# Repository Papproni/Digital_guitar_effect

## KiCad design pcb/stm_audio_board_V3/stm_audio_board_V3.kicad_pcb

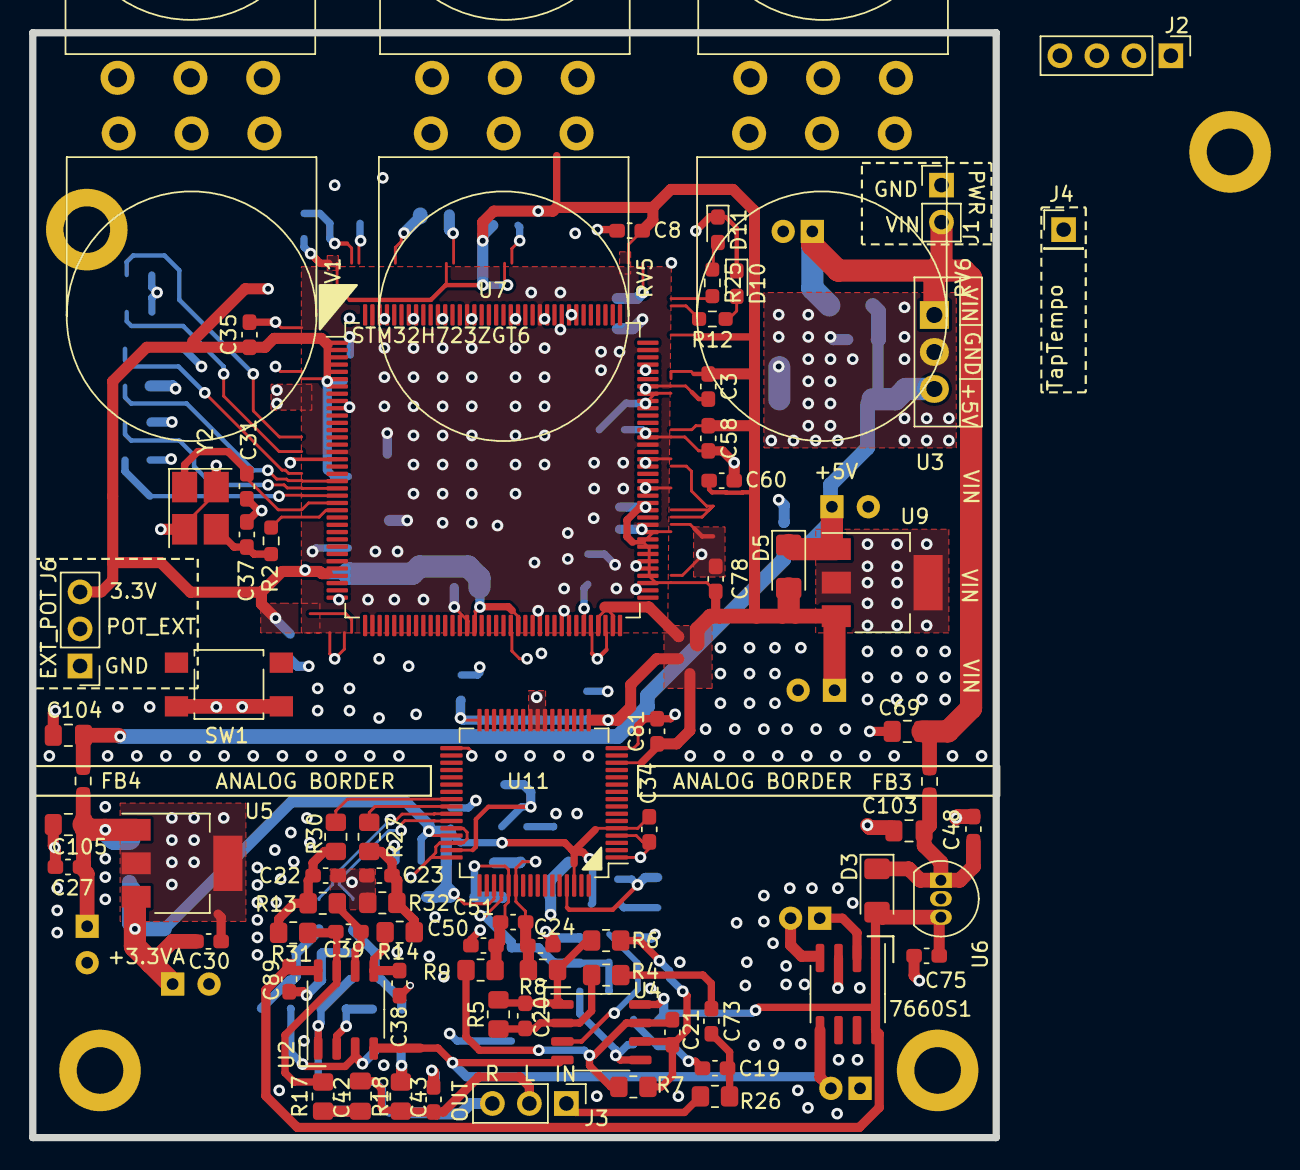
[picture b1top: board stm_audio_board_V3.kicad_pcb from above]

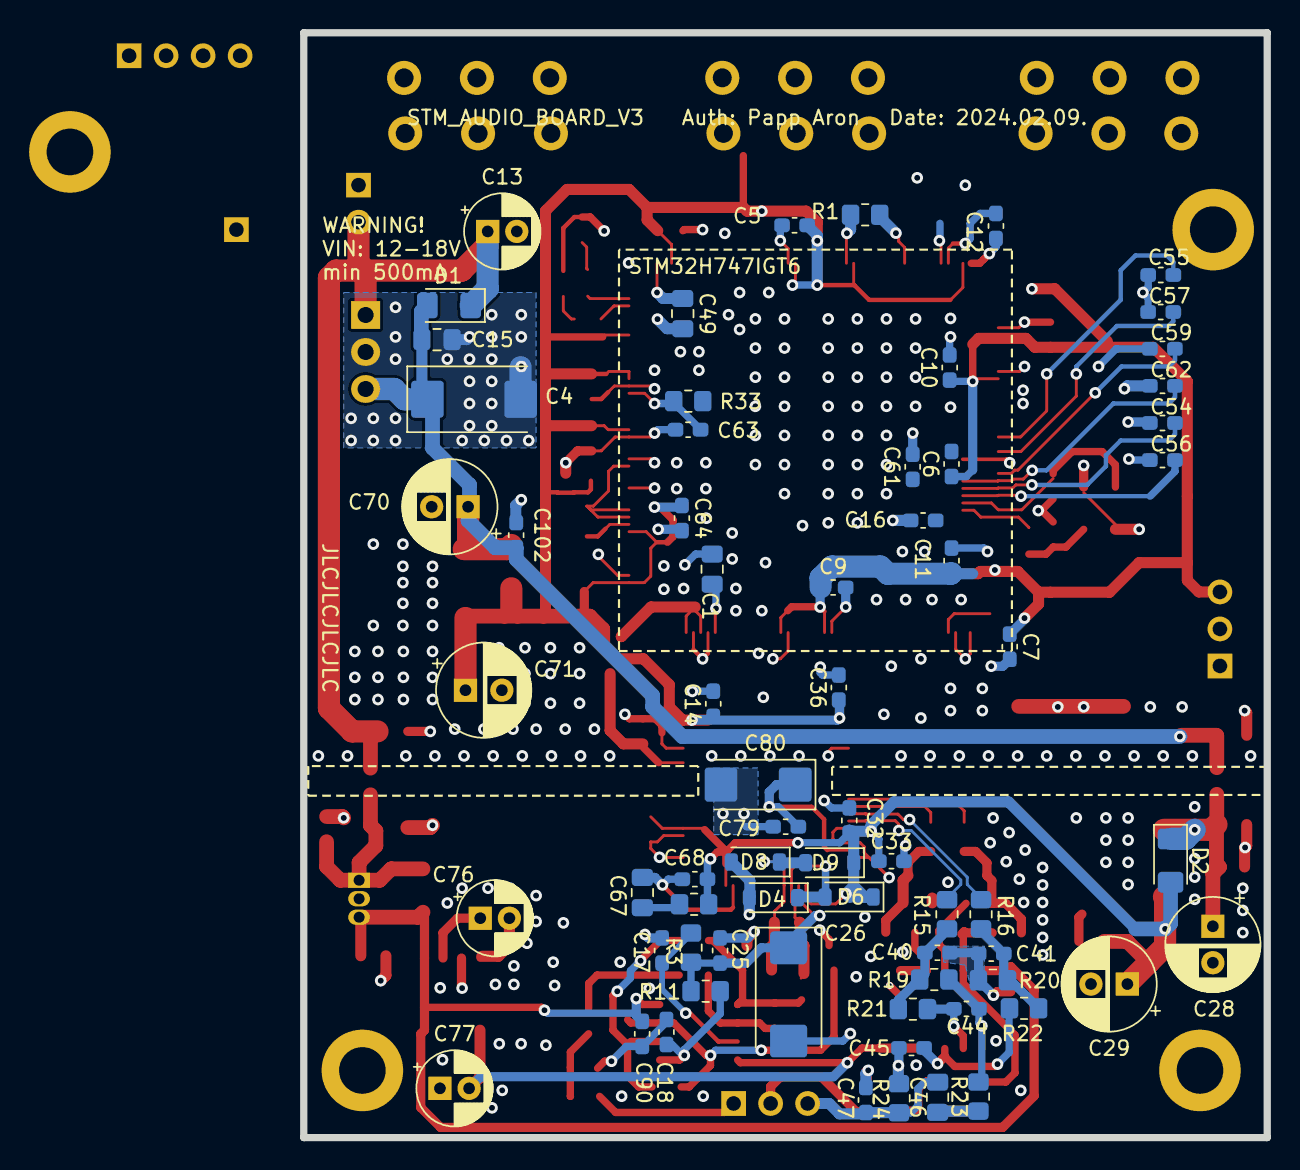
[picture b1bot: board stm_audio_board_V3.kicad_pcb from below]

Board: 4 copper layers, 66.1 x 75.8 mm, 149 parts (67 on the bottom side), 71 nets.

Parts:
7660S1: SOIC-8_3.9x4.9mm_P1.27mm
C1, C49: 2.2uF; C_0805_2012Metric_Pad1.18x1.45mm_HandSolder
C3, C5, C6, C7, C8, C9, C10, C11, C12, C14, C16, C25, C27, C30, C32, C33, C34, C35, C36, C48, C54, C55, C56, C57, C58, C59, C60, C61, C62, C63, C64, C75, C78, C79, C81, C89, C90, C102: 100nF; C_0603_1608Metric_Pad1.08x0.95mm_HandSolder
C4: 22uF tantal; CP_EIA-7343-31_Kemet-D_Pad2.25x2.55mm_HandSolder
C13: 22uF 50V poly; CP_Radial_D5.0mm_P2.00mm
C15, C69, C103, C104, C105: 2u2F; C_0805_2012Metric_Pad1.18x1.45mm_HandSolder
C17, C18, C73: 68n; C_0603_1608Metric_Pad1.08x0.95mm_HandSolder
C19, C20: 10p; C_0603_1608Metric_Pad1.08x0.95mm_HandSolder
C21: 120p; C_0603_1608Metric_Pad1.08x0.95mm_HandSolder
C22, C40: 270p; C_0603_1608Metric_Pad1.08x0.95mm_HandSolder
C23, C41: 560p; C_0603_1608Metric_Pad1.08x0.95mm_HandSolder
C24, C50: 1nF; C_0603_1608Metric_Pad1.08x0.95mm_HandSolder
C26: 47uF tantal; CP_EIA-7343-31_Kemet-D_Pad2.25x2.55mm_HandSolder
C28, C70: 100uF; CP_Radial_D6.3mm_P2.50mm
C29: 47uF; CP_Radial_D6.3mm_P2.50mm
C31, C37: 9pF; C_0603_1608Metric_Pad1.08x0.95mm_HandSolder
C38, C39, C44, C45: 68p; C_0603_1608Metric_Pad1.08x0.95mm_HandSolder
C42, C46: 2u2; C_0805_2012Metric_Pad1.18x1.45mm_HandSolder
C43, C47, C68: 2.2nF; C_0603_1608Metric_Pad1.08x0.95mm_HandSolder
C51: 100pF; C_0603_1608Metric_Pad1.08x0.95mm_HandSolder
C67: 39nF; C_0805_2012Metric_Pad1.18x1.45mm_HandSolder
C71: 47uf; CP_Radial_D6.3mm_P2.50mm
C76, C77: 10uF; CP_Radial_D5.0mm_P2.00mm
C80: 10uF tantal; CP_EIA-6032-28_Kemet-C_Pad2.25x2.35mm_HandSolder
D1, D2, D3, D5: 1N4148; D_1206_3216Metric_Pad1.42x1.75mm_HandSolder
D4, D6, D8, D9: BAT42W-V; D_SOD-123
D10, D11: LED; LED_0603_1608Metric_Pad1.05x0.95mm_HandSolder
FB3, FB4: TDK MMZ1608R601ATD25 DB; R_0603_1608Metric_Pad0.98x0.95mm_HandSolder
H1, H2, H3, H4: MountingHole_Pad; MountingHole_3.2mm_M3_DIN965_Pad
J1: Power conn; PinHeader_1x02_P2.54mm_Vertical
J2: STlink; PinHeader_1x04_P2.54mm_Vertical
J3: Audio_sig; PinHeader_1x03_P2.54mm_Vertical
J4: Conn_01x01_taptempo; PinHeader_1x01_P2.54mm_Vertical
J6: Conn_01x03_pot_ext; PinHeader_1x03_P2.54mm_Vertical
R1, R18, R24: 10k; R_0805_2012Metric_Pad1.20x1.40mm_HandSolder
R2: 100R NC; R_0603_1608Metric_Pad0.98x0.95mm_HandSolder
R3, R11: 100R; R_0805_2012Metric_Pad1.20x1.40mm_HandSolder
R4, R33: 500k; R_0805_2012Metric_Pad1.20x1.40mm_HandSolder
R5: 1M; R_0805_2012Metric_Pad1.20x1.40mm_HandSolder
R6, R7: 5.76k; R_0805_2012Metric_Pad1.20x1.40mm_HandSolder
R8, R9: 240R; R_0805_2012Metric_Pad1.20x1.40mm_HandSolder
R10: 3.32k; R_0805_2012Metric_Pad1.20x1.40mm_HandSolder
R12: 1k NC; R_0603_1608Metric_Pad0.98x0.95mm_HandSolder
R13, R21: 3k; R_0805_2012Metric_Pad1.20x1.40mm_HandSolder
R14, R22: 1.5k; R_0805_2012Metric_Pad1.20x1.40mm_HandSolder
R15, R19, R30, R31: 11k; R_0805_2012Metric_Pad1.20x1.40mm_HandSolder
R16, R20, R27, R32: 5.6k; R_0805_2012Metric_Pad1.20x1.40mm_HandSolder
R17, R23: 604; R_0805_2012Metric_Pad1.20x1.40mm_HandSolder
R25: 1k; R_0603_1608Metric_Pad0.98x0.95mm_HandSolder
R26: 100; R_0805_2012Metric_Pad1.20x1.40mm_HandSolder
RV1, RV2, RV3, RV4, RV5, RV6: R_Potentiometer; Potentiometer_Omeg_PC16BU_Vertical
SW1: SW_SPST; SW_SPST_TL3305A
U2, U4: OP275; SSOP-8_3.9x5.05mm_P1.27mm
U3: MP-K7805-500R3; TO-220-3_Vertical
U5, U9: MIC2920A-3.3WS-TR; SOT-223-3_TabPin2
U6: L7809; TO-92_Inline
U7: STM32H723ZGTx; LQFP-144_20x20mm_P0.5mm
U11: LQFP-64_10x10mm_P0.5mm
Y2: X1E0000210132; Crystal_SMD_SeikoEpson_TSX3225-4Pin_3.2x2.5mm_HandSoldering

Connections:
5V: C4.1, C15.1, C70.1, C102.1, C104.1, D1.2 (A), D5.1 (K), FB4.1, U3.3 (OUT), U9.1 (VI)
+3.3V: C3.1, C5.1, C6.1, C7.1, C8.1, C9.1, C10.1, C11.1, C12.1, C14.1, C35.1, C36.1, C58.1, C60.1, C64.1, C71.1, C78.1, C81.1, D5.2 (A), J2.4, J6.3, RV1.1, RV2.1, RV3.1, RV4.1, RV5.1, RV6.1, U7.6 (VBAT), U7.17 (VDD), U7.30 (VDD), U7.32 (VREF+), U7.33 (VDDA), U7.39 (VDD), U7.52 (VDD), U7.62 (VDD), U7.72 (VDD), U7.84 (VDD), U7.95 (VDD33USB), U7.108 (VDD), U7.121 (VDD), U7.131 (VDD), U7.144 (VDD), U9.3 (VO), U11.14 (PD/RST), U11.17 (DVDD), U11.32 (DVDD)
+3.3VA: C29.1, C30.1, C32.1, C33.1, C34.1, C68.1, D2.2 (A), D6.1 (K), D9.1 (K), R10.2, U5.3 (VO), U11.5 (AVDD), U11.45 (AVDD), U11.51 (AVDD), U11.62 (AVDD)
+9V: 7660S1.1 (BOOST), 7660S1.8 (V+), C75.1, C89.1, C90.1, D3.2 (A), U2.8 (V+), U4.8 (V+), U6.3 (OUT)
-9V: 7660S1.5 (VOUT), C77.2, U2.4 (V-), U4.4 (V-)
/MCU/NRST: C16.1, SW1.1 (A), U7.25 (NRST)
AD1939_CM: C25.2, C26.1, R3.2, R11.2, U11.52 (CM)
AD1939_FILTR: C79.2, C80.1, U11.47 (FILTR)
AD1939_I2S1_CK: U7.69 (PB10), U11.28 (ABCLK)
AD1939_I2S1_SDI: U7.28 (PC2_C), U11.27 (ASDATA1)
AD1939_I2S1_WS: U7.73 (PB12), U11.29 (ALRCLK)
AD1939_I2S2_CK: U7.111 (PC10), U11.21 (DBCLK)
AD1939_I2S2_SDO: U7.48 (PB2), U11.19 (DSDATA2)
AD1939_I2S2_WS: U7.40 (PA4), U11.22 (DLRCLK)
AD1939_LF: C67.2, C68.2, U11.61 (LF)
AD1939_SPI3_CLK: U7.41 (PA5), U11.34 (CCLK)
AD1939_SPI3_MISO: U7.42 (PA6), U11.31 (COUT)
AD1939_SPI3_MOSI: U7.43 (PA7), U11.30 (CIN)
ADC1N: C24.2, C51.2, D8.1 (K), D9.2 (A), R8.1, U11.54 (ADC1LN)
ADC1P: C50.1, C51.1, D4.1 (K), D6.2 (A), R9.1, U11.53 (ADC1LP)
DAC1N: R27.1, U11.41 (OL2N)
DAC1P: R30.1, U11.40 (OL2P)
DAC2N: R15.1, U11.43 (OR2N)
DAC2P: R16.1, U11.42 (OR2P)
EXT_INT_BUTTON: C63.2, R33.1
GND: 7660S1.3 (GND), C1.2, C3.2, C4.2, C5.2, C6.2, C7.2, C8.2, C9.2, C10.2, C11.2, C12.2, C13.2, C14.2, C15.2, C16.2, C17.2, C18.2, C19.1, C22.1, C23.2, C24.1, C25.1, C26.2, C27.2, C28.2, C29.2, C30.2, C31.1, C32.2, C33.2, C34.2, C35.2, C36.2, C37.1, C38.1, C40.1, C41.2, C43.1, C45.1, C47.1, C48.2, C49.2, C50.2, C54.2, C55.2, C56.2, C57.2, C58.2, C59.2, C60.2, C61.2, C62.2, C63.1, C64.2, C69.2, C70.2, C71.2, C75.2, C77.1, C78.2, C79.1, C80.2, C81.2, C89.2, C90.2, C102.2, C103.2, C104.2, C105.2, D4.2 (A), D8.2 (A), D10.1 (K), D11.1 (K), H1.1, H2.1, H3.1, H4.1, J1.1, J2.1, J6.1, R1.2, R18.2, R20.1, R24.2, R32.1, RV1.3, RV2.3, RV3.3, RV4.3, RV5.3, RV6.3, SW1.2 (B), U3.2 (GND), U5.2 (GND), U6.2 (GND), U7.16 (VSS), U7.31 (VSSA), U7.38 (VSS), U7.51 (VSS), U7.61 (VSS), U7.83 (VSS), U7.94 (VSS), U7.107 (VSS), U7.120 (VSS), U7.130 (VSS), U7.143 (PDR_ON), U9.2 (GND), U11.1 (AGND), U11.4 (AGND), U11.16 (DGND), U11.23 (VSUPPLY), U11.24 (VSENSE), U11.25 (VDRIVE), U11.33 (DGND), U11.44 (AGND), U11.46 (AGND), U11.48 (AGND), Y2.2, Y2.4
GUITAR_IN: J3.1, R26.1
GUITAR_OUT_L/MONO: C42.2, C43.2, J3.2, R18.1
GUITAR_OUT_R: C46.2, C47.2, J3.3, R24.1
unnamed: 7660S1.2 (CAP+), C76.1
unnamed: 7660S1.4 (CAP-), C76.2
unnamed: C1.1, U7.71 (VCAP)
unnamed: C19.2, C73.2, R26.2
unnamed: C20.2, R5.1, R6.2, R8.2, U4.1
unnamed: C21.2, R7.1, R9.2, U4.7
unnamed: C22.2, R13.1, R30.2, R31.1
unnamed: C23.1, R14.2, R27.2, R32.2
unnamed: C37.2, R2.2, Y2.3
unnamed: C39.2, R17.2, R31.2, U2.7
unnamed: C40.2, R15.2, R19.1, R21.2
unnamed: C41.1, R16.2, R20.2, R22.2
unnamed: C42.1, R17.1
unnamed: C44.2, R19.2, R23.2, U2.1
unnamed: C46.1, R23.1
unnamed: C49.1, U7.106 (VCAP)
unnamed: C67.1, R10.1
unnamed: C73.1, R4.2
unnamed: C27.1, C28.1, C105.1, D2.1 (K), FB4.2, U5.1 (VI)
unnamed: C48.1, C103.1, D3.1 (K), FB3.2, U6.1 (IN)
unnamed: D10.2 (A), R12.1
unnamed: D11.2 (A), R25.1
unnamed: C45.2, R22.1, U2.3 (+)
unnamed: C44.1, R21.1, U2.2 (-)
unnamed: C38.2, R14.1, U2.5 (+)
unnamed: C39.1, R13.2, U2.6 (-)
unnamed: C17.1, R3.1, U4.3 (+)
unnamed: C20.1, R4.1, R5.2, U4.2 (-)
unnamed: C18.1, R11.1, U4.5 (+)
unnamed: C21.1, R6.1, R7.2, U4.6 (-)
unnamed: R1.1, U7.138 (BOOT0)
OSC0: C31.2, U7.23 (PH0), Y2.1
OSC1: R2.1, U7.24 (PH1)
POT1: C55.1, RV1.2, U7.13 (PF3)
POT2: C57.1, RV2.2, U7.15 (PF5)
POT3: C59.1, RV3.2, U7.19 (PF7)
POT4: C62.1, RV4.2, U7.20 (PF8)
POT5: C54.1, RV5.2, U7.21 (PF9)
POT6: C56.1, RV6.2, U7.22 (PF10)
POT_EXT: C61.1, J6.2
PWR_INPUT_12V-18V: C13.1, C69.1, D1.1 (K), FB3.1, J1.2, U3.1 (IN)
TAP_TEMPO_INPUT: J4.1, R33.2

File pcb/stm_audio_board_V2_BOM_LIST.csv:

Designator,Comment,Footprint,LCSC
7660S1,~,Package_SO:SOIC-8_3.9x4.9mm_P1.27mm,
"C1, C2, C49, C52",2.2uF,Capacitor_SMD:C_0805_2012Metric_Pad1.18x1.45mm_HandSolder,
"C3, C5, C6, C7, C8, C9, C10, C11, C12, C14, C25, C30, C32, C33, C34, C35, C36, C54, C55, C56, C57, C58, C59, C60, C61, C62, C63, C64, C75, C78, C79, C81, C89, C90, C102",100nF,Capacitor_SMD:C_0603_1608Metric_Pad1.08x0.95mm_HandSolder,
C4,22uF tantal,Capacitor_Tantalum_SMD:CP_EIA-7343-31_Kemet-D_Pad2.25x2.55mm_HandSolder,
C13,22uF 50V poly,Capacitor_THT:CP_Radial_D5.0mm_P2.00mm,
"C15, C69, C103, C104, C105",2u2F,Capacitor_SMD:C_0805_2012Metric_Pad1.18x1.45mm_HandSolder,
"C16, C27, C48",100nF ,Capacitor_SMD:C_0603_1608Metric_Pad1.08x0.95mm_HandSolder,
"C17, C18, C73",68n,Capacitor_SMD:C_0603_1608Metric_Pad1.08x0.95mm_HandSolder,
C19,220p,Capacitor_SMD:C_0603_1608Metric_Pad1.08x0.95mm_HandSolder,
"C20, C21",120p,Capacitor_SMD:C_0603_1608Metric_Pad1.08x0.95mm_HandSolder,
"C22, C40",270p,Capacitor_SMD:C_0603_1608Metric_Pad1.08x0.95mm_HandSolder,
"C23, C41",560p,Capacitor_SMD:C_0603_1608Metric_Pad1.08x0.95mm_HandSolder,
"C24, C50",1nF,Capacitor_SMD:C_0603_1608Metric_Pad1.08x0.95mm_HandSolder,
C26,100uF tantal,Capacitor_Tantalum_SMD:CP_EIA-7343-31_Kemet-D_Pad2.25x2.55mm_HandSolder,
"C28, C70",100uF,Capacitor_THT:CP_Radial_D6.3mm_P2.50mm,
C29,47uF,Capacitor_THT:CP_Radial_D6.3mm_P2.50mm,
"C31, C37",7pF,Capacitor_SMD:C_0603_1608Metric_Pad1.08x0.95mm_HandSolder,
"C38, C39, C44, C45",68p,Capacitor_SMD:C_0603_1608Metric_Pad1.08x0.95mm_HandSolder,
"C42, C46",2u2,Capacitor_SMD:C_0805_2012Metric_Pad1.18x1.45mm_HandSolder,
"C43, C47",2.2nF,Capacitor_SMD:C_0603_1608Metric_Pad1.08x0.95mm_HandSolder,
C51,100pF,Capacitor_SMD:C_0603_1608Metric_Pad1.08x0.95mm_HandSolder,
"C65, C66",12p,Capacitor_SMD:C_0603_1608Metric_Pad1.08x0.95mm_HandSolder,
C67,5.6nF,Capacitor_SMD:C_0805_2012Metric_Pad1.18x1.45mm_HandSolder,
C68,390pF,Capacitor_SMD:C_0603_1608Metric_Pad1.08x0.95mm_HandSolder,
C71,47uf,Capacitor_THT:CP_Radial_D6.3mm_P2.50mm,
"C76, C77",10uF,Capacitor_THT:CP_Radial_D5.0mm_P2.00mm,
C80,10uF tantal,Capacitor_SMD:C_0805_2012Metric_Pad1.18x1.45mm_HandSolder,
"D1, D2, D3, D5",1N4148,Diode_SMD:D_1206_3216Metric_Pad1.42x1.75mm_HandSolder,
D7,LED,LED_SMD:LED_SK6805_PLCC4_2.4x2.7mm_P1.3mm,
"FB3, FB4",TDK MMZ1608R601ATD25 DB,Resistor_SMD:R_0603_1608Metric_Pad0.98x0.95mm_HandSolder,
"H1, H2, H3, H4",MountingHole_Pad,MountingHole:MountingHole_3.2mm_M3_DIN965_Pad,
J1,Power conn,Connector_PinHeader_2.54mm:PinHeader_1x02_P2.54mm_Vertical,
J2,STlink,Connector_PinHeader_2.54mm:PinHeader_1x04_P2.54mm_Vertical,
J3,Audio_sig,Connector_PinHeader_2.54mm:PinHeader_1x03_P2.54mm_Vertical,
J4,Conn_01x01_taptempo,Connector_PinHeader_2.54mm:PinHeader_1x01_P2.54mm_Vertical,
J5,Conn_01x10_display,Connector_PinHeader_2.54mm:PinHeader_1x10_P2.54mm_Vertical,
J6,Conn_01x03_pot_ext,Connector_PinHeader_2.54mm:PinHeader_1x03_P2.54mm_Vertical,
J7,Conn_01x8_pots_internal,Connector_PinHeader_2.54mm:PinHeader_1x08_P2.54mm_Vertical,
"R1, R18, R24, R28",10k,Resistor_SMD:R_0805_2012Metric_Pad1.20x1.40mm_HandSolder,
"R3, R11",100R,Resistor_SMD:R_0805_2012Metric_Pad1.20x1.40mm_HandSolder,
"R4, R33",500k,Resistor_SMD:R_0805_2012Metric_Pad1.20x1.40mm_HandSolder,
R5,1M,Resistor_SMD:R_0805_2012Metric_Pad1.20x1.40mm_HandSolder,
"R6, R7",5.76k,Resistor_SMD:R_0805_2012Metric_Pad1.20x1.40mm_HandSolder,
"R8, R9",240R,Resistor_SMD:R_0805_2012Metric_Pad1.20x1.40mm_HandSolder,
R10,562,Resistor_SMD:R_0805_2012Metric_Pad1.20x1.40mm_HandSolder,
"R13, R21",3k,Resistor_SMD:R_0805_2012Metric_Pad1.20x1.40mm_HandSolder,
"R14, R22",1.5k,Resistor_SMD:R_0805_2012Metric_Pad1.20x1.40mm_HandSolder,
"R15, R19, R30, R31",11k,Resistor_SMD:R_0805_2012Metric_Pad1.20x1.40mm_HandSolder,
"R16, R20, R27, R32",5.6k,Resistor_SMD:R_0805_2012Metric_Pad1.20x1.40mm_HandSolder,
"R17, R23",604,Resistor_SMD:R_0805_2012Metric_Pad1.20x1.40mm_HandSolder,
R26,100,Resistor_SMD:R_0805_2012Metric_Pad1.20x1.40mm_HandSolder,
SW1,SW_SPST,Button_Switch_SMD:SW_SPST_TL3305A,
U1,STM32H747IGTx,Package_QFP:LQFP-176_24x24mm_P0.5mm,
"U2, U4",OP275,Package_SO:SSOP-8_3.9x5.05mm_P1.27mm,
U3,MP-K7805-500R3,Package_TO_SOT_THT:TO-220-3_Vertical,
"U5, U9",MIC2920A-3.3WS-TR,Package_TO_SOT_SMD:SOT-223-3_TabPin2,
U6,L7809,Package_TO_SOT_THT:TO-92_Inline,
U11,~,Package_QFP:LQFP-64_10x10mm_P0.5mm,
Y1,Crystal_GND24,Crystal:Crystal_SMD_5032-4Pin_5.0x3.2mm,
Y2,X1E0000210132,Crystal:Crystal_SMD_SeikoEpson_TSX3225-4Pin_3.2x2.5mm_HandSoldering,

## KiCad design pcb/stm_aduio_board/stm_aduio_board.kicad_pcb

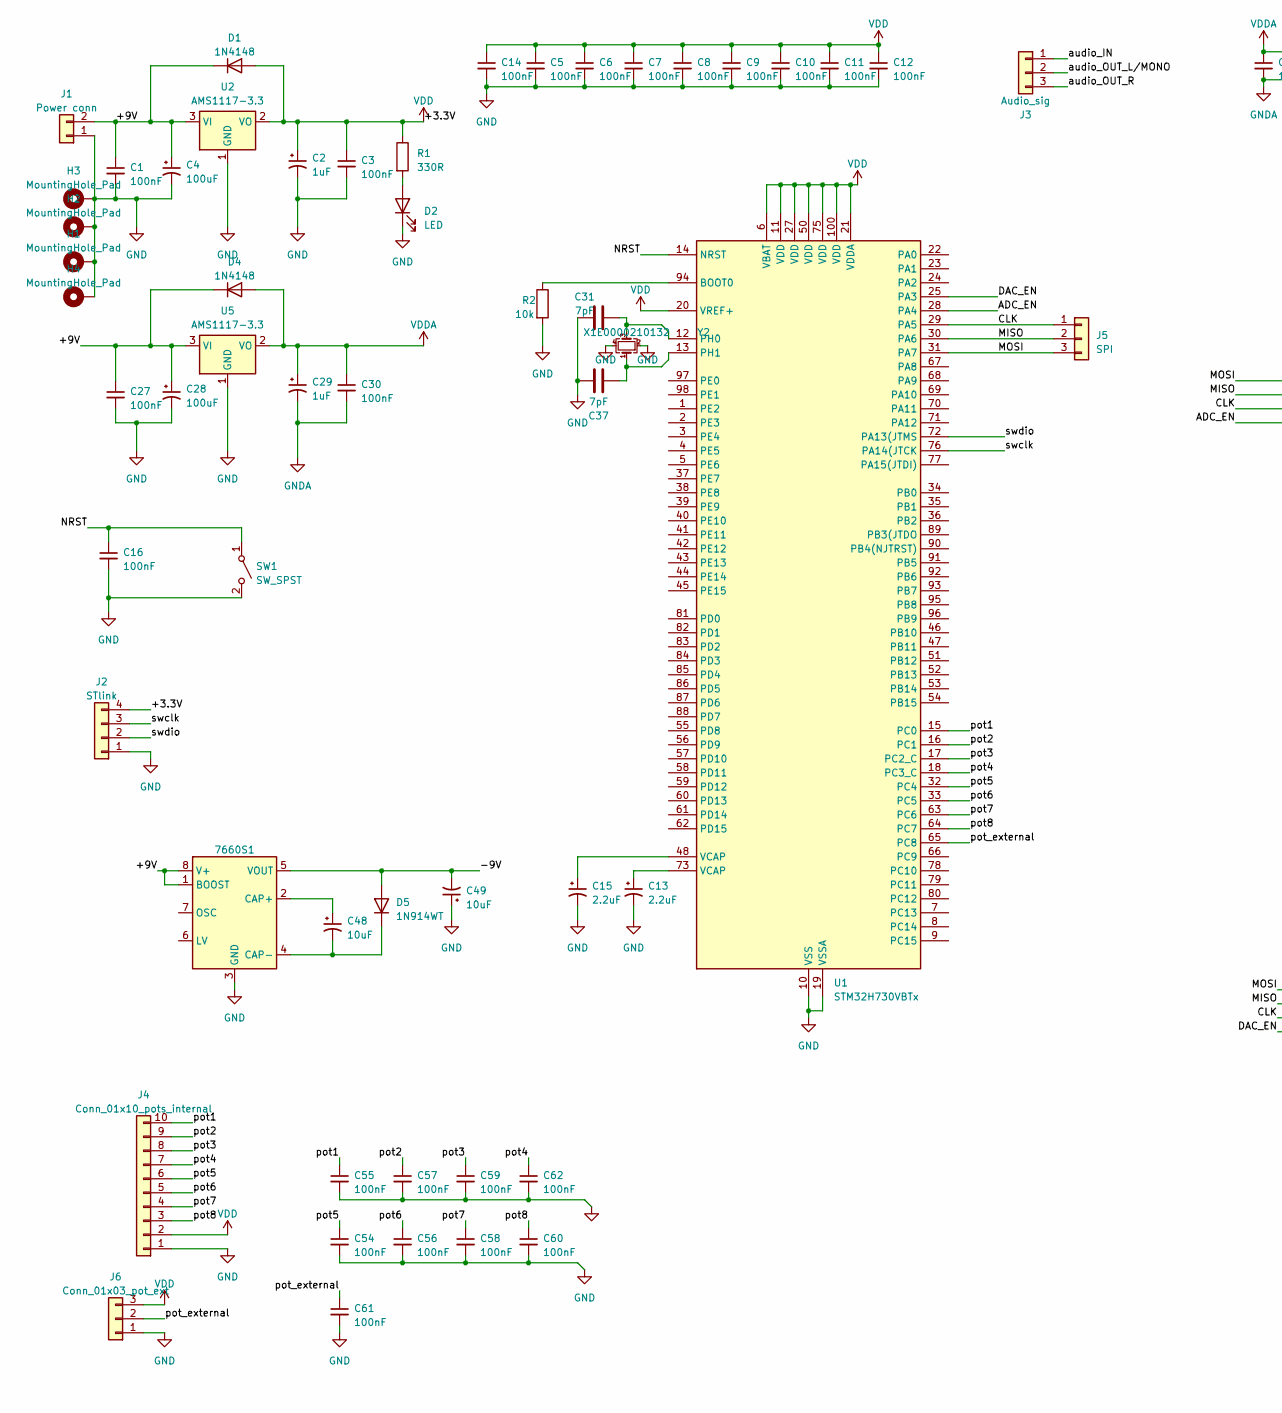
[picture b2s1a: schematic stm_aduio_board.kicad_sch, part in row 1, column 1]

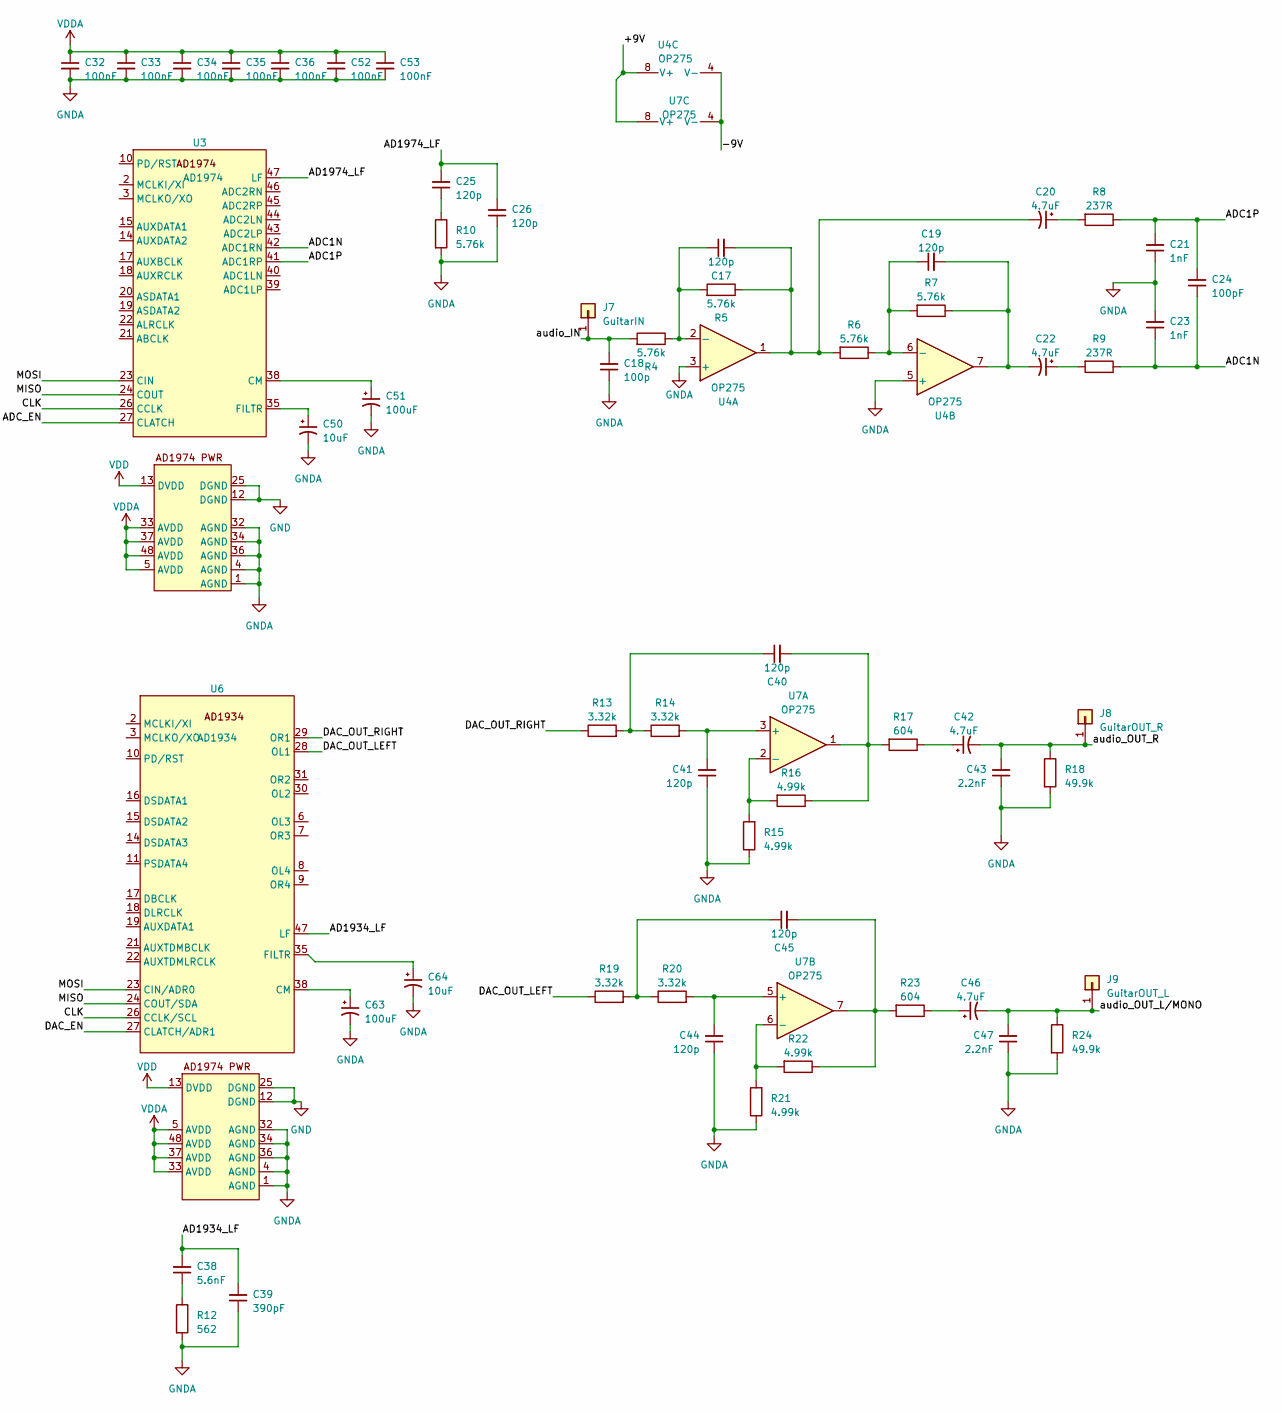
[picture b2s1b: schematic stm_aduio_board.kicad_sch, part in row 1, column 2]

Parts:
7660S1: SOIC-8_3.9x4.9mm_P1.27mm
C1, C3, C5, C6, C7, C8, C9, C10, C11, C12, C14, C16, C27, C30, C32, C33, C34, C35, C36, C52, C53, C54, C55, C56, C57, C58, C59, C60, C61, C62: 100nF; C_0603_1608Metric_Pad1.08x0.95mm_HandSolder
C2, C29: 1uF; CP_Radial_D6.3mm_P2.50mm
C4, C28: 100uF; CP_Radial_D6.3mm_P2.50mm
C13, C15: 2.2uF; C_0805_2012Metric_Pad1.18x1.45mm_HandSolder
C17, C19, C25, C26, C40, C41, C44, C45: 120p; C_0603_1608Metric_Pad1.08x0.95mm_HandSolder
C18: 100p; C_0603_1608Metric_Pad1.08x0.95mm_HandSolder
C20, C22, C42, C46: 4.7uF; C_0805_2012Metric_Pad1.18x1.45mm_HandSolder
C21, C23: 1nF; C_0603_1608Metric_Pad1.08x0.95mm_HandSolder
C24: 100pF; C_0603_1608Metric_Pad1.08x0.95mm_HandSolder
C31, C37: 7pF; C_0603_1608Metric_Pad1.08x0.95mm_HandSolder
C38: 5.6nF; C_0603_1608Metric_Pad1.08x0.95mm_HandSolder
C39: 390pF; C_0603_1608Metric_Pad1.08x0.95mm_HandSolder
C43, C47: 2.2nF; C_0603_1608Metric_Pad1.08x0.95mm_HandSolder
C48: 10uF; CP_Radial_D6.3mm_P2.50mm
C49, C50, C64: 10uF; C_1210_3225Metric_Pad1.33x2.70mm_HandSolder
C51, C63: 100uF; C_1210_3225Metric_Pad1.33x2.70mm_HandSolder
D1, D4: 1N4148; D_DO-35_SOD27_P7.62mm_Horizontal
D2: LED; LED_SK6805_PLCC4_2.4x2.7mm_P1.3mm
D5: 1N914WT; D_SOD-523
H1, H2, H3, H4: MountingHole_Pad; MountingHole_3.2mm_M3
J1: Power conn; PinHeader_1x02_P2.54mm_Vertical
J2: STlink; PinHeader_1x04_P2.54mm_Vertical
J3: Audio_sig; PinHeader_1x03_P2.54mm_Vertical
J4: Conn_01x10_pots_internal; PinHeader_1x10_P2.54mm_Vertical
J5: SPI; PinHeader_1x03_P2.54mm_Vertical
J6: Conn_01x03_pot_ext; PinHeader_1x03_P2.54mm_Vertical
J7: GuitarIN; PinHeader_1x01_P2.54mm_Vertical
J8: GuitarOUT_R; PinHeader_1x01_P2.54mm_Vertical
J9: GuitarOUT_L; PinHeader_1x01_P2.54mm_Vertical
R1: 330R; R_0805_2012Metric_Pad1.20x1.40mm_HandSolder
R2: 10k; R_0805_2012Metric_Pad1.20x1.40mm_HandSolder
R4, R5, R6, R7, R10: 5.76k; R_0805_2012Metric_Pad1.20x1.40mm_HandSolder
R8, R9: 237R; R_0805_2012Metric_Pad1.20x1.40mm_HandSolder
R12: 562; R_0805_2012Metric_Pad1.20x1.40mm_HandSolder
R13, R14, R19, R20: 3.32k; R_0805_2012Metric_Pad1.20x1.40mm_HandSolder
R15, R16, R21, R22: 4.99k; R_0805_2012Metric_Pad1.20x1.40mm_HandSolder
R17, R23: 604; R_0805_2012Metric_Pad1.20x1.40mm_HandSolder
R18, R24: 49.9k; R_0805_2012Metric_Pad1.20x1.40mm_HandSolder
SW1: SW_SPST; SW_SPST_TL3305A
U1: STM32H730VBTx; LQFP-100_14x14mm_P0.5mm
U2, U5: AMS1117-3.3; SOT-223-3_TabPin2
U3: AD1974; LQFP-48_7x7mm_P0.5mm
U4, U7: OP275; SSOP-8_3.9x5.05mm_P1.27mm
U6: AD1934; LQFP-48_7x7mm_P0.5mm
Y2: X1E0000210132; Crystal_SMD_SeikoEpson_TSX3225-4Pin_3.2x2.5mm_HandSoldering

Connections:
/+9V: 7660S1.1 (BOOST), 7660S1.8 (V+), C1.1, C4.1, C27.1, C28.1, D1.1 (K), D4.1 (K), J1.2, U2.3 (VI), U4.8 (V+), U5.3 (VI), U7.8 (V+)
/-9V: 7660S1.5 (VOUT), C49.2, D5.2 (A), U4.4 (V-), U7.4 (V-)
/AD1934_LF: C38.2, C39.2, U6.47 (LF)
/AD1974_LF: C25.2, C26.2, U3.47 (LF)
/ADC1N: C23.1, C24.1, R9.1, U3.42 (ADC1RN)
/ADC1P: C21.2, C24.2, R8.1, U3.41 (ADC1RP)
/ADC_EN: U1.28 (PA4), U3.27 (CLATCH)
/CLK: J5.1, U1.29 (PA5), U3.26 (CCLK), U6.26 (CCLK/SCL)
/DAC_EN: U1.25 (PA3), U6.27 (CLATCH/ADR1)
/DAC_OUT_LEFT: R19.1, U6.28 (OL1)
/DAC_OUT_RIGHT: R13.1, U6.29 (OR1)
/MISO: J5.2, U1.30 (PA6), U3.24 (COUT), U6.24 (COUT/SDA)
/MOSI: J5.3, U1.31 (PA7), U3.23 (CIN), U6.23 (CIN/ADR0)
/NRST: C16.1, SW1.1 (A), U1.14 (NRST)
/audio_IN: C18.2, J3.1, J7.1, R4.2
/audio_OUT_L/MONO: C46.2, C47.2, J3.2, J9.1, R24.1
/audio_OUT_R: C42.2, C43.2, J3.3, J8.1, R18.1
/pot1: C55.1, J4.10, U1.15 (PC0)
/pot2: C57.1, J4.9, U1.16 (PC1)
/pot3: C59.1, J4.8, U1.17 (PC2_C)
/pot4: C62.1, J4.7, U1.18 (PC3_C)
/pot5: C54.1, J4.6, U1.32 (PC4)
/pot6: C56.1, J4.5, U1.33 (PC5)
/pot7: C58.1, J4.4, U1.63 (PC6)
/pot8: C60.1, J4.3, U1.64 (PC7)
/pot_external: C61.1, J6.2, U1.65 (PC8)
/swclk: J2.3, U1.76 (PA14(JTCK)
/swdio: J2.2, U1.72 (PA13(JTMS)
GND: 7660S1.3 (GND), C1.2, C2.2, C3.2, C4.2, C5.2, C6.2, C7.2, C8.2, C9.2, C10.2, C11.2, C12.2, C13.2, C14.2, C15.2, C16.2, C27.2, C28.2, C31.1, C37.1, C49.1, C54.2, C55.2, C56.2, C57.2, C58.2, C59.2, C60.2, C61.2, C62.2, D2.1 (K), H1.1, H2.1, H3.1, H4.1, J1.1, J2.1, J4.1, J6.1, R2.2, SW1.2 (B), U1.10 (VSS), U1.19 (VSSA), U1.26 (VSS), U1.49 (VSS), U1.74 (VSS), U1.99 (VSS), U2.1 (GND), U3.12 (DGND), U3.25 (DGND), U5.1 (GND), U6.12 (DGND), U6.25 (DGND), Y2.2, Y2.4
GNDA: C18.1, C21.1, C23.2, C26.1, C29.2, C30.2, C32.2, C33.2, C34.2, C35.2, C36.2, C39.1, C41.1, C43.1, C44.1, C47.1, C50.2, C51.2, C52.2, C53.2, C63.2, C64.2, R10.2, R12.2, R15.1, R18.2, R21.1, R24.2, U3.1 (AGND), U3.4 (AGND), U3.32 (AGND), U3.34 (AGND), U3.36 (AGND), U4.3 (+), U4.5 (+), U6.1 (AGND), U6.4 (AGND), U6.32 (AGND), U6.34 (AGND), U6.36 (AGND)
unnamed: 7660S1.2 (CAP+), C48.1
unnamed: 7660S1.4 (CAP-), C48.2, D5.1 (K)
unnamed: C13.1, U1.73 (VCAP)
unnamed: C15.1, U1.48 (VCAP)
unnamed: C17.2, C20.2, R5.1, R6.2, U4.1
unnamed: C19.2, C22.2, R7.1, U4.7
unnamed: C20.1, R8.2
unnamed: C22.1, R9.2
unnamed: C25.1, R10.1
unnamed: C38.1, R12.1
unnamed: C40.1, R13.2, R14.1
unnamed: C40.2, R16.1, R17.2, U7.1
unnamed: C42.1, R17.1
unnamed: C45.1, R19.2, R20.1
unnamed: C45.2, R22.1, R23.2, U7.7
unnamed: C46.1, R23.1
unnamed: D2.2 (A), R1.2
unnamed: R2.1, U1.94 (BOOT0)
unnamed: C31.2, U1.12 (PH0), Y2.3
unnamed: C37.2, U1.13 (PH1), Y2.1
unnamed: C51.1, U3.38 (CM)
unnamed: C50.1, U3.35 (FILTR)
unnamed: C17.1, R4.1, R5.2, U4.2 (-)
unnamed: C19.1, R6.1, R7.2, U4.6 (-)
unnamed: C63.1, U6.38 (CM)
unnamed: C64.1, U6.35 (FILTR)
unnamed: C41.2, R14.2, U7.3 (+)
unnamed: R15.2, R16.2, U7.2 (-)
unnamed: C44.2, R20.2, U7.5 (+)
unnamed: R21.2, R22.2, U7.6 (-)
VDD: C2.1, C3.1, C5.1, C6.1, C7.1, C8.1, C9.1, C10.1, C11.1, C12.1, C14.1, D1.2 (A), J2.4, J4.2, J6.3, R1.1, U1.6 (VBAT), U1.11 (VDD), U1.20 (VREF+), U1.21 (VDDA), U1.27 (VDD), U1.50 (VDD), U1.75 (VDD), U1.100 (VDD), U2.2 (VO), U3.13 (DVDD), U6.13 (DVDD)
VDDA: C29.1, C30.1, C32.1, C33.1, C34.1, C35.1, C36.1, C52.1, C53.1, D4.2 (A), U3.5 (AVDD), U3.33 (AVDD), U3.37 (AVDD), U3.48 (AVDD), U5.2 (VO), U6.5 (AVDD), U6.33 (AVDD), U6.37 (AVDD), U6.48 (AVDD)

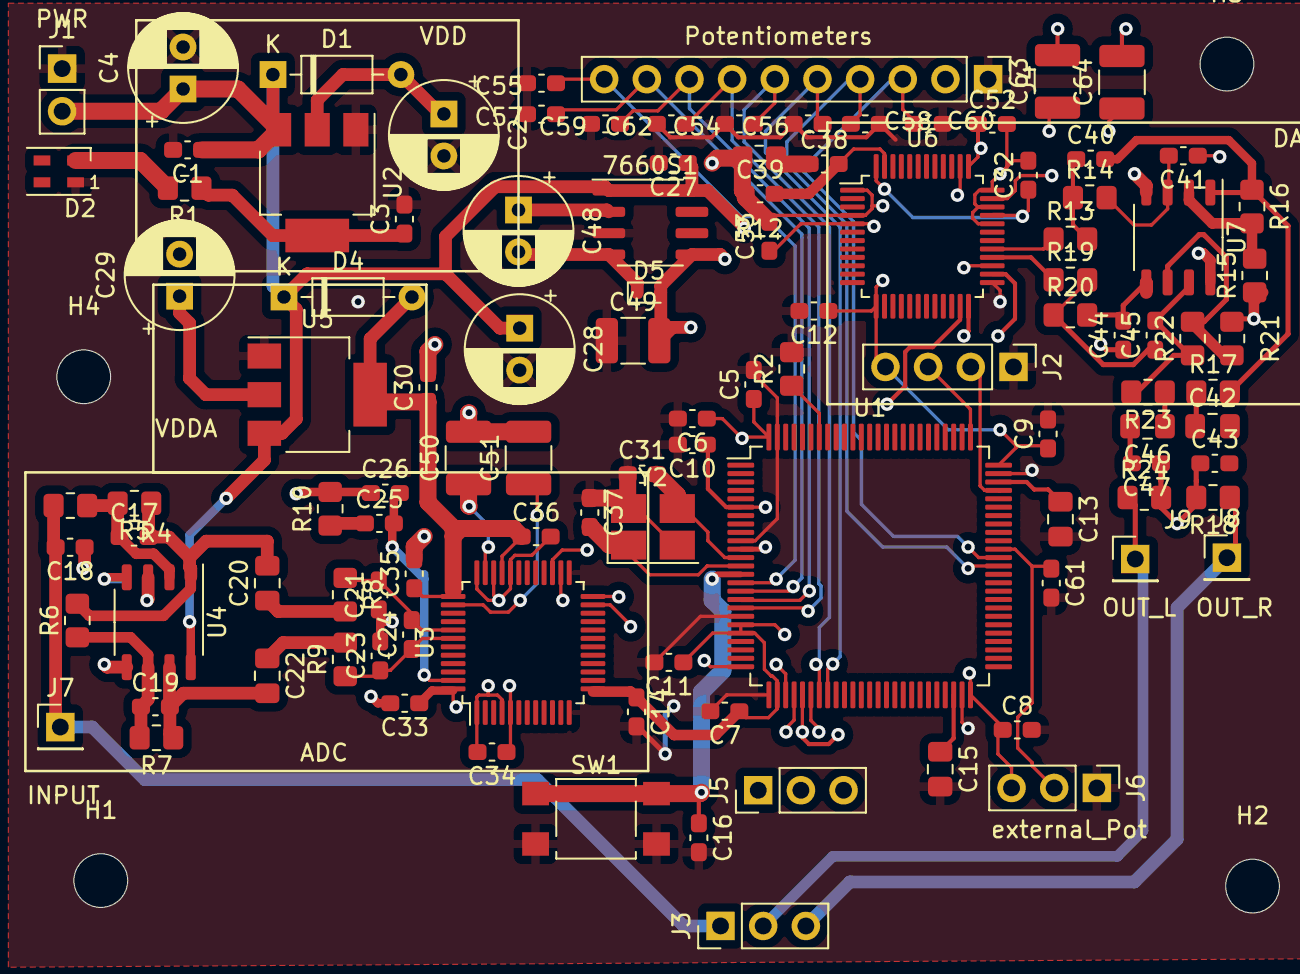
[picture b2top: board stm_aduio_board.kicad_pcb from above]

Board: 4 copper layers, 113 parts (0 on the bottom side), 62 nets.

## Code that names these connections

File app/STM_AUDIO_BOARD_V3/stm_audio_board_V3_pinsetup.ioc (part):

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Mcu.Name=STM32H723ZGTx
Mcu.Package=LQFP144
Mcu.UserName=STM32H723ZGTx
PA4.Mode=Half_Duplex_Master_Tx
PA4.Signal=I2S3_WS
PA5.Mode=Full_Duplex_Master
PA5.Signal=SPI1_SCK
PA6.Mode=Full_Duplex_Master
PA6.Signal=SPI1_MISO
PA7.Mode=Full_Duplex_Master
PA7.Signal=SPI1_MOSI
PB10.Mode=Half_Duplex_Master_Rx
PB10.Signal=I2S2_CK
PB12.Mode=Half_Duplex_Master_Rx
PB12.Signal=I2S2_WS
PB2.Mode=Half_Duplex_Master_Tx
PB2.Signal=I2S3_SDO
PC10.Mode=Half_Duplex_Master_Tx
PC10.Signal=I2S3_CK
PC2_C.Mode=Half_Duplex_Master_Rx
PC2_C.Signal=I2S2_SDI
PF10.Mode=IN6-Single-Ended
PF10.Signal=ADC3_INP6
PF3.Mode=IN5-Single-Ended
PF3.Signal=ADC3_INP5
PF5.Mode=IN4-Single-Ended
PF5.Signal=ADC3_INP4
PF7.Mode=IN3-Single-Ended
PF7.Signal=ADC3_INP3
PF8.Mode=IN7-Single-Ended
PF8.Signal=ADC3_INP7
PF9.Mode=IN2-Single-Ended
PF9.Signal=ADC3_INP2
PH0-OSC_IN.Mode=HSE-External-Oscillator
PH0-OSC_IN.Signal=RCC_OSC_IN
PH1-OSC_OUT.Mode=HSE-External-Oscillator
PH1-OSC_OUT.Signal=RCC_OSC_OUT
RCC.SYSCLKFreq_VALUE=550000000
RCC.SYSCLKSource=RCC_SYSCLKSOURCE_PLLCLK
board=custom

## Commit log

2023-09-16 add documents
2023-09-16 Add pcb design from last semester
2023-09-16 Add matlab scripts from last semester
2023-09-16 add projects from last semester
2023-09-16 Added basic template for signal processing in Matlab
2023-09-16 add all my scripts written for the previous project
2023-09-18 add new version of pcb project
2023-09-18 Schematic divided into pages, Global connectors added
2023-09-20 in_between_commit
2023-09-20 add simulation folder, input and output simulation is done
2023-09-23 Simualtion refined
2023-09-24 added choke to analog pwr, created 5 V rail, decided to pivot and use codec instead dedicated hardware
2023-09-24 testing offset sim, and changing layout
2023-09-24 Update AD1939_input_with_offset.asc, AD1939_input_with_offset.net, and 6 more files...
2023-09-27 Update AD1939_input_with_offset.asc, AD1939_input_with_offset.log, and 8 more files...
2023-09-27 AD1939 input stage is done for good
2023-09-27 pdf export added
2023-09-28 ad1939 input stage update
2023-09-28 add ad1939
2023-09-28 ad1939 symbol added
2023-09-28 pcb design update
2023-09-28 ad1939 symbol
2023-09-28 Revert "ad1939 symbol"
    This reverts commit 4681f4fc206e9d714606101e66803f3fb06a48b5.
2023-09-28 ad1939 symbol is finished
2023-09-28 Update #auto_saved_files#, Power.kicad_sch, and 6 more files...
2023-09-30 input and output stage reworked in sim and in schematic, power filtering is changed, further calculations needed
2023-09-30 Update _autosave-stm_audio_board_V2.kicad_pcb, stm_audio_board_V2-2023-09-30_190513.zip, and 3 more files...
2023-10-01 Update ad1939_dif.log, ad1939_dif.op.raw, and 6 more files...
2023-10-04 PCB design started INPUT and OUTPUT stage done, codec placed
2023-10-04 Update #auto_saved_files#, Connectors.kicad_sch, and 18 more files...
2023-10-05 trace widening
2023-10-07 codec osc ground reroute
2023-10-16 Update stm_audio_board_V2-2023-10-05_151559.zip, stm_audio_board_V2-2023-10-07_140250.zip, and 11 more files...
2023-10-18 smps setup is used
2023-10-19 Revert "smps setup is used"
    This reverts commit c545ff16c6c59c28f3eb4762b27085b24475d59c.
2023-10-19 Revert "Update stm_audio_board_V2-2023-10-05_151559.zip, stm_audio_board_V2-2023-10-07_140250.zip, and 11 more files..."
    This reverts commit add49324ea034b1afd9ddd0c8b7f42af87af436b.
2023-10-19 STM32h747igt6 is added and smps is NOT used
2023-10-19 saving
2023-10-19 BOM list with links is added (not finished)
2023-10-19 MIC2920A symbol is created
2023-10-19 electrical mA reqs listed briefly
2023-10-22 ILI9341 testing project added for stm32h755ziq dev board usign spi3
2023-10-22 Update .mxproject, .cproject, and 804 more files...
2023-10-24 Update .mxproject, subdir.mk, and 1078 more files...
2023-10-25 pinout added, pcb is updated according to pinout excel
2023-10-30 pinsetup ready
2023-11-01 Capacitor types are choosen, schematic updated, unused capacitors deleted. Connectors need to be connected to the mcu and its finished
2023-11-01 pcb seems to be finished drc error: 0
2023-11-01 Update stm_audio_board_V2-B_Cu.gbr, stm_audio_board_V2-B_Mask.gbr, and 14 more files...
2023-11-02 updated pcb design
2023-11-02 Update stm_audio_board_V2-B_Cu.gbr, stm_audio_board_V2-B_Mask.gbr, and 29 more files...
2023-11-02 silkscreen updated
2023-11-03 Update output_not_finished.zip, stm_audio_board_V2-B_Cu.gbl, and 44 more files...
2023-11-03 added vias and overall fixes around pcb
2023-11-03 stm_audio_board_V2 is finished, sent to jlcPCB for production
2023-11-23 basic library added
2023-11-24 touchgfx fixes
2023-12-02 touchGFX works!!!!
2023-12-09 errors found in PCB output stage, codec driver developement started
2023-12-10 ad1939_init defined
2023-12-10 some pcb errors are labeled
2023-12-10 i2s testing in main for DAC
2023-12-10 i2s left align
2024-01-15 First working project
    The AD1939 PLL loop changed for DBCLK pll input, the ad1939 now works as a slave, the stm32 i2s interfaces are masters (errata). The PLL loop needs VDD not GND!!!!
2024-01-15 Octave project added
    Project created, DSP library added to workspace
2024-01-19 Double buffering is used!
    octave_test:
    double buffering is used
    clear output signal for effect and passthrough
2024-01-20 double octave added
2024-01-20 added more subbands to octave
2024-01-20 fixed erb subband calculations, and octave effect params
2024-01-23 Dcache is not working yet
2024-01-23 Octave calculations fixed
2024-01-23 Double buffer and Dcache is working
2024-01-25 guitar_effect object and its structs are created
    These are not functional yet
2024-02-01 minor fixes
2024-02-01 delay developement started
2024-02-01 modulation added to delay
2024-02-07 stm_audio_board_v2_1 kicad project added
    This project is aimed to fix problems experienced in v2
2024-02-07 pcb notes added for developement
2024-02-07 fixes in pcb
2024-02-07 changes applied to delay effect
2024-02-08 audo_board v2_1 output stage is reworked
2024-02-09 input stage is done, fixes for the audioboardV2_1 over
2024-02-09 audio_board_v3 added
2024-02-09 nothing
2024-02-13 potmeter for V3 changed
2024-02-15 stm32h723 project for pinout added
2024-02-16 SUB octave added
2024-02-18 octave effect library started
2024-02-20 v3 pcb updated pinout generated form cubeide
2024-02-24 jack mount output pcb created
2024-02-24 octave library developement
2024-02-24 Hal lib access is fixed in octave_test project
2024-02-25 submodules added
    submodules for pcb and projects are created
2024-02-25 submodule updated
2024-02-25 added pdfs docs
2024-02-25 usb code debugging
2024-03-01 Octave up is working
2024-03-02 working on ffect stacks
